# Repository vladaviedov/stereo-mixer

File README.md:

# Stereo Mixer

Design files for my [stereo mixer
project](https://vladaviedov.org/project/stereo_mixer.html).

## KiCad

### Third-Party Libraries

The following libraries cannot be distributed and need to be manually
downloaded.

- [PJ-037A](https://www.sameskydevices.com/product/resource/digikeypcbfootprint/pj-037a) -> `kicad/lib/PJ-037A`

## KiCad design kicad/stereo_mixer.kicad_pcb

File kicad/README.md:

# Stereo Mixer PCB

This is the design from my audio stereo mixer project.

## Third-Party Libraries

The following libraries cannot be distributed and need to be manually
downloaded.

- [PJ-037A](https://www.sameskydevices.com/product/resource/digikeypcbfootprint/pj-037a) -> `lib/PJ-037A`

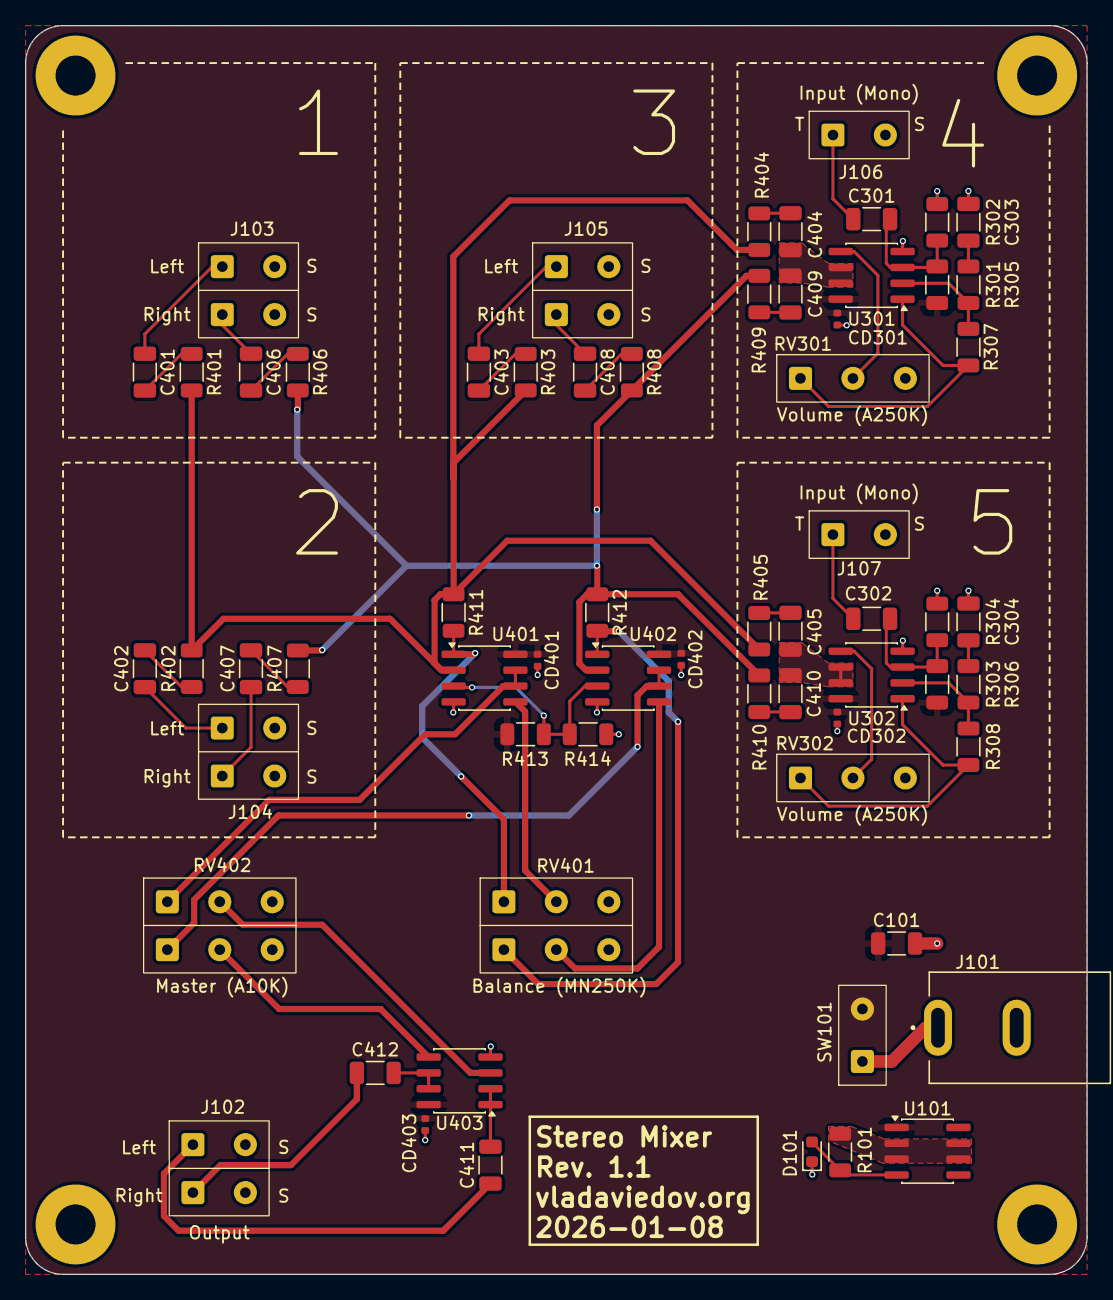
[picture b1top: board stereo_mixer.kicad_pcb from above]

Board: 2 copper layers, 85.0 x 100.0 mm, 68 parts (0 on the bottom side), 50 nets.

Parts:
C101, C303, C304, C411, C412: 10uF; C_1206_3216Metric
C301, C302, C401, C402, C403, C404, C405, C406, C407, C408, C409, C410: 0.1uF; C_1206_3216Metric
CD301, CD302, CD401, CD402, CD403: 0.1uF; C_0402_1005Metric_Fix
D101: Green; LED_0603_1608Metric
H101, H102, H103, H104: M3; MountingHole_3.2mm_M3_Pad
J101: DC In; CUI_PJ-037A
J102: Output; ChassisMount_Wire-0.25sqmm_2x02_P4.2mm_D0.65mm_OD1.7mm
J103: Input CH1; ChassisMount_Wire-0.25sqmm_2x02_P4.2mm_D0.65mm_OD1.7mm
J104: Input CH2; ChassisMount_Wire-0.25sqmm_2x02_P4.2mm_D0.65mm_OD1.7mm
J105: Input CH3; ChassisMount_Wire-0.25sqmm_2x02_P4.2mm_D0.65mm_OD1.7mm
J106: Input CH4; ChassisMount_Wire-0.25sqmm_1x02_P4.2mm_D0.65mm_OD1.7mm
J107: Input CH5; ChassisMount_Wire-0.25sqmm_1x02_P4.2mm_D0.65mm_OD1.7mm
R101: 220; R_1206_3216Metric
R301, R302, R303, R304: 470k; R_1206_3216Metric
R305, R306: 2.2k; R_1206_3216Metric
R307, R308: 220k; R_1206_3216Metric
R401, R402, R403, R404, R405, R406, R407, R408, R409, R410, R411, R412, R413, R414: 100k; R_1206_3216Metric
RV301, RV302: A250K; ChassisMount_Wire-0.25sqmm_1x03_P4.2mm_D0.65mm_OD1.7mm
RV401: MN250K; ChassisMount_Wire-0.25sqmm_2x03_P4.2mm_D0.65mm_OD1.7mm
RV402: A10K; ChassisMount_Wire-0.25sqmm_2x03_P4.2mm_D0.65mm_OD1.7mm
SW101: SPST; ChassisMount_Wire-0.25sqmm_1x02_P4.2mm_D0.65mm_OD1.7mm
U101: LM317L_SO8; SOIC-8_3.9x4.9mm_P1.27mm
U301, U302, U401, U402, U403: LM358; SOIC-8_3.9x4.9mm_P1.27mm

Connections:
/CH1.L: C401.1, J103.1
/CH1.R: C406.1, J103.3
/CH2.L: C402.1, J104.1
/CH2.R: C407.1, J104.3
/CH3.L: C403.1, J105.1
/CH3.R: C408.1, J105.3
/CH4: C301.1, J106.1
/CH5: C302.1, J107.1
/Mixers/CH4.L: C404.1, C409.1, U301.6 (-), U301.7
/Mixers/CH5.L: C405.1, C410.1, U302.6 (-), U302.7
/Mixers/VREF: R413.2, R414.1, U401.3 (+), U402.3 (+)
/OUT.L: C411.1, J102.1
/OUT.R: C412.1, J102.3
GND: C101.2, C303.2, C304.2, CD301.2, CD302.2, CD401.2, CD402.2, CD403.2, D101.1 (K), H101.1, H102.1, H103.1, H104.1, J101.2, J102.2, J102.4, J103.2, J103.4, J104.2, J104.4, J105.2, J105.4, J106.2, J107.2, R302.2, R304.2, R414.2, RV301.3, RV302.3, RV401.3, RV401.6, RV402.3, RV402.6, U301.4 (V-), U302.4 (V-), U401.4 (V-), U402.4 (V-), U403.4 (V-)
unnamed: C303.1, R305.2
unnamed: C304.1, R306.2
unnamed: C401.2, R401.1
unnamed: C402.2, R402.1
unnamed: C403.2, R403.1
unnamed: C404.2, R404.1
unnamed: C405.2, R405.1
unnamed: C406.2, R406.1
unnamed: C407.2, R407.1
unnamed: C408.2, R408.1
unnamed: C409.2, R409.1
unnamed: C410.2, R410.1
unnamed: D101.2 (A), R101.2, U101.4 (ADJ)
unnamed: R101.1, U101.2 (VO), U101.3 (VO), U101.6 (VO), U101.7 (VO)
unnamed: R307.2, RV301.1, U301.1
unnamed: R308.2, RV302.1, U302.1
unnamed: R411.2, RV401.1, U401.1
unnamed: R412.2, RV401.4, U402.1
unnamed: J101.1, SW101.1 (A)
unnamed: C301.2, R301.2, R302.1, U301.3 (+)
unnamed: R305.1, R307.1, U301.2 (-)
unnamed: RV301.2, U301.5 (+)
unnamed: C302.2, R303.2, R304.1, U302.3 (+)
unnamed: R306.1, R308.1, U302.2 (-)
unnamed: RV302.2, U302.5 (+)
unnamed: R401.2, R402.2, R403.2, R404.2, R405.2, R411.1, U401.2 (-)
unnamed: RV401.2, U401.5 (+)
unnamed: RV402.1, U401.6 (-), U401.7
unnamed: R406.2, R407.2, R408.2, R409.2, R410.2, R412.1, U402.2 (-)
unnamed: RV401.5, U402.5 (+)
unnamed: RV402.4, U402.6 (-), U402.7
unnamed: RV402.2, U403.3 (+)
unnamed: C411.2, U403.1, U403.2 (-)
unnamed: RV402.5, U403.5 (+)
unnamed: C412.2, U403.6 (-), U403.7
VCC: C101.1, CD301.1, CD302.1, CD401.1, CD402.1, CD403.1, R301.1, R303.1, R413.1, SW101.2 (B), U101.1 (VI), U301.8 (V+), U302.8 (V+), U401.8 (V+), U402.8 (V+), U403.8 (V+)

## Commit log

2025-12-22 add design files for rev 1.0
2025-12-22 add pcb release for rev 1.0
2025-12-22 move README
2025-12-22 add license
2026-01-07 add custom chassis mounting footprints
2026-01-07 split ch4 and ch5 connectors, update footprints
2026-01-08 replace electrolytic caps with ceramics
2026-01-08 fix symbol library links
2026-01-08 change led to smt, update schematic rev
2026-01-08 update preamp potentiometer footprints
2026-01-08 modify stereo channel footprints
2026-01-08 redesign pcb for 1.1
2026-01-10 add rev1.1 release
2026-02-17 ignore kicad_prl file
